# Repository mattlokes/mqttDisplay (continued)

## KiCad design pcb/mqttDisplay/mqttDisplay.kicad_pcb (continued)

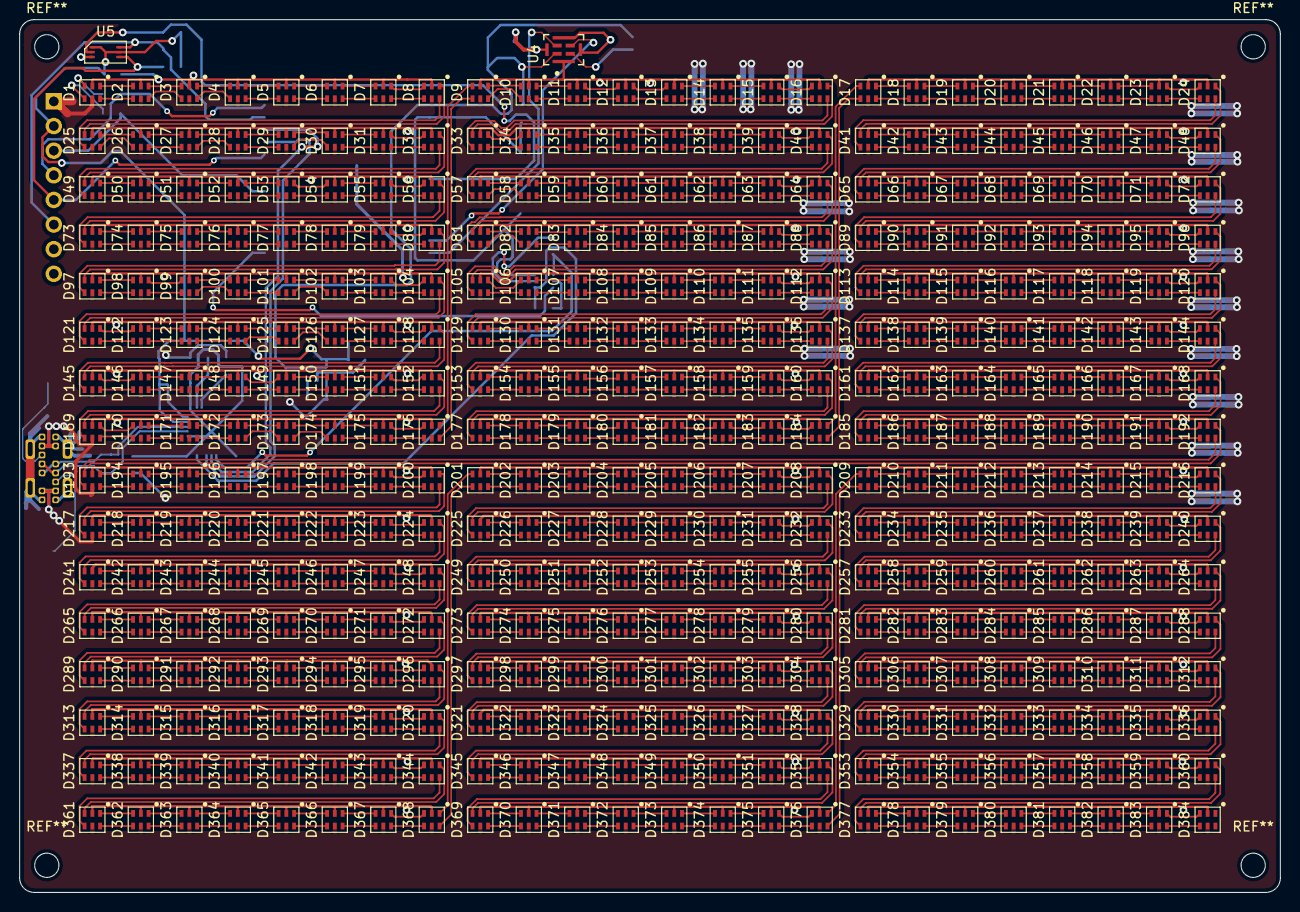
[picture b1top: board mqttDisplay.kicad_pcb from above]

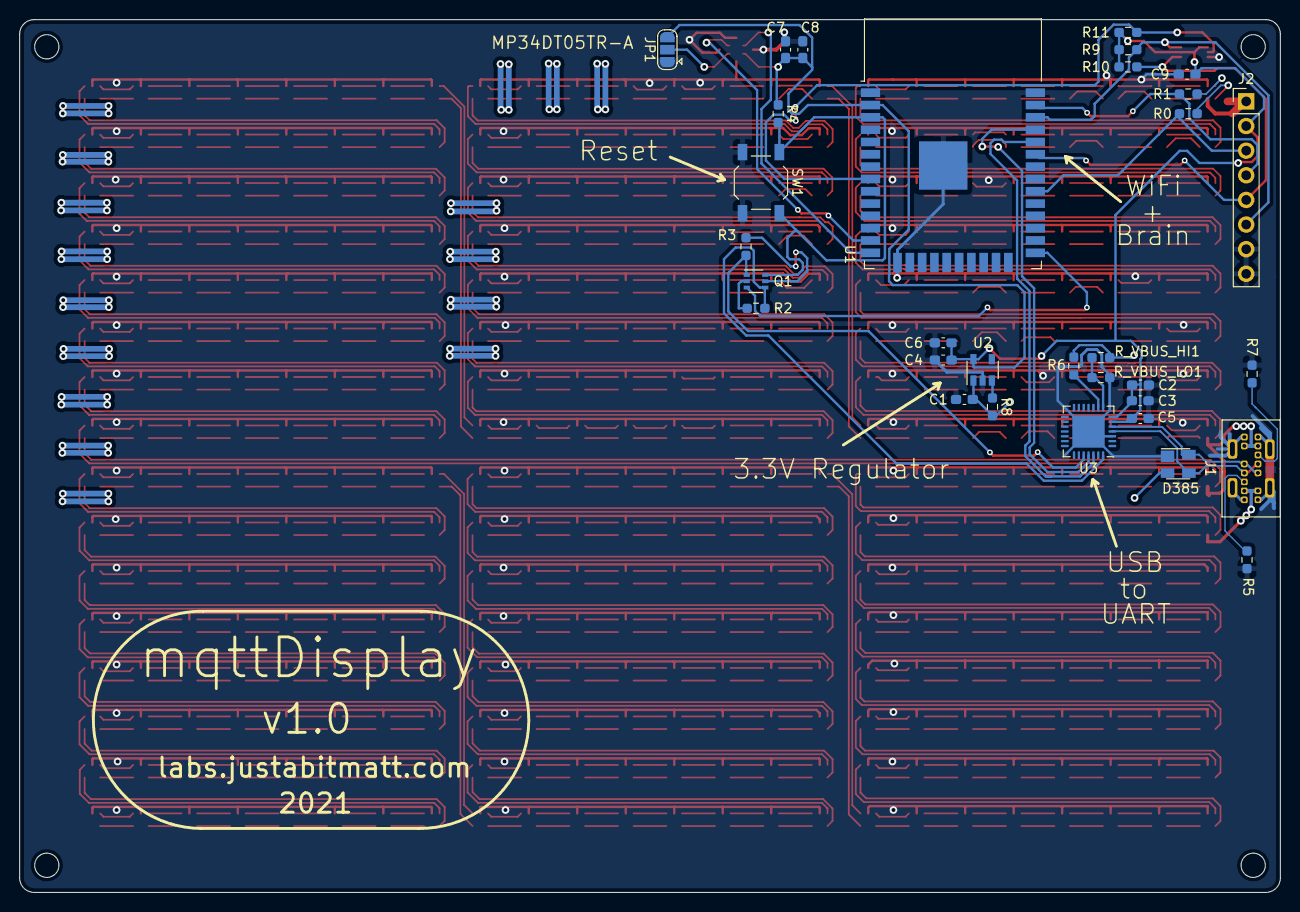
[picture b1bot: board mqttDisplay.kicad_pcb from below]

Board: 2 copper layers, 130.0 x 90.0 mm, 418 parts (32 on the bottom side), 794 nets.

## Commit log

2021-02-14 Swap tool scripts for a simple Makefile
2021-02-14 Makeflow can initialise the ESP32 with micropython using targt esp32-init
2021-02-14 Add working colour to makefile target prints, add python file upload/serial attach targets
2021-02-14 MQTT subscribing to correct topics and printing new message values
2021-02-14 Get Display working across 4 boards, concept proven
2021-02-19 Add Adagruit GFX Library, add NeoPixelPanel class for converting panels to display, remove a load of things, improve makefile, got it working
2021-03-14 Add V1.0 PCB
2021-03-28 Add interactive bom
2021-03-28 Add case STLs and 3mf files
2021-03-28 Add schematic
2021-04-04 Migrate to SK9822 (APA102) display
2021-04-05 Add Animation Buffer Objects to allow easier anmiation programming, add Battery guage graphic
2021-04-10 Untested commit of restructure of content, into views and view control to allow differnt content to be displayed
2021-04-11 The big reshuffle/refactor, better organised and easier to develop
2021-04-11 KiCaD project changes
2021-04-11 Get refactored coded working again with views
2021-04-11 Add Clock view and fix some of the view control round robin system
